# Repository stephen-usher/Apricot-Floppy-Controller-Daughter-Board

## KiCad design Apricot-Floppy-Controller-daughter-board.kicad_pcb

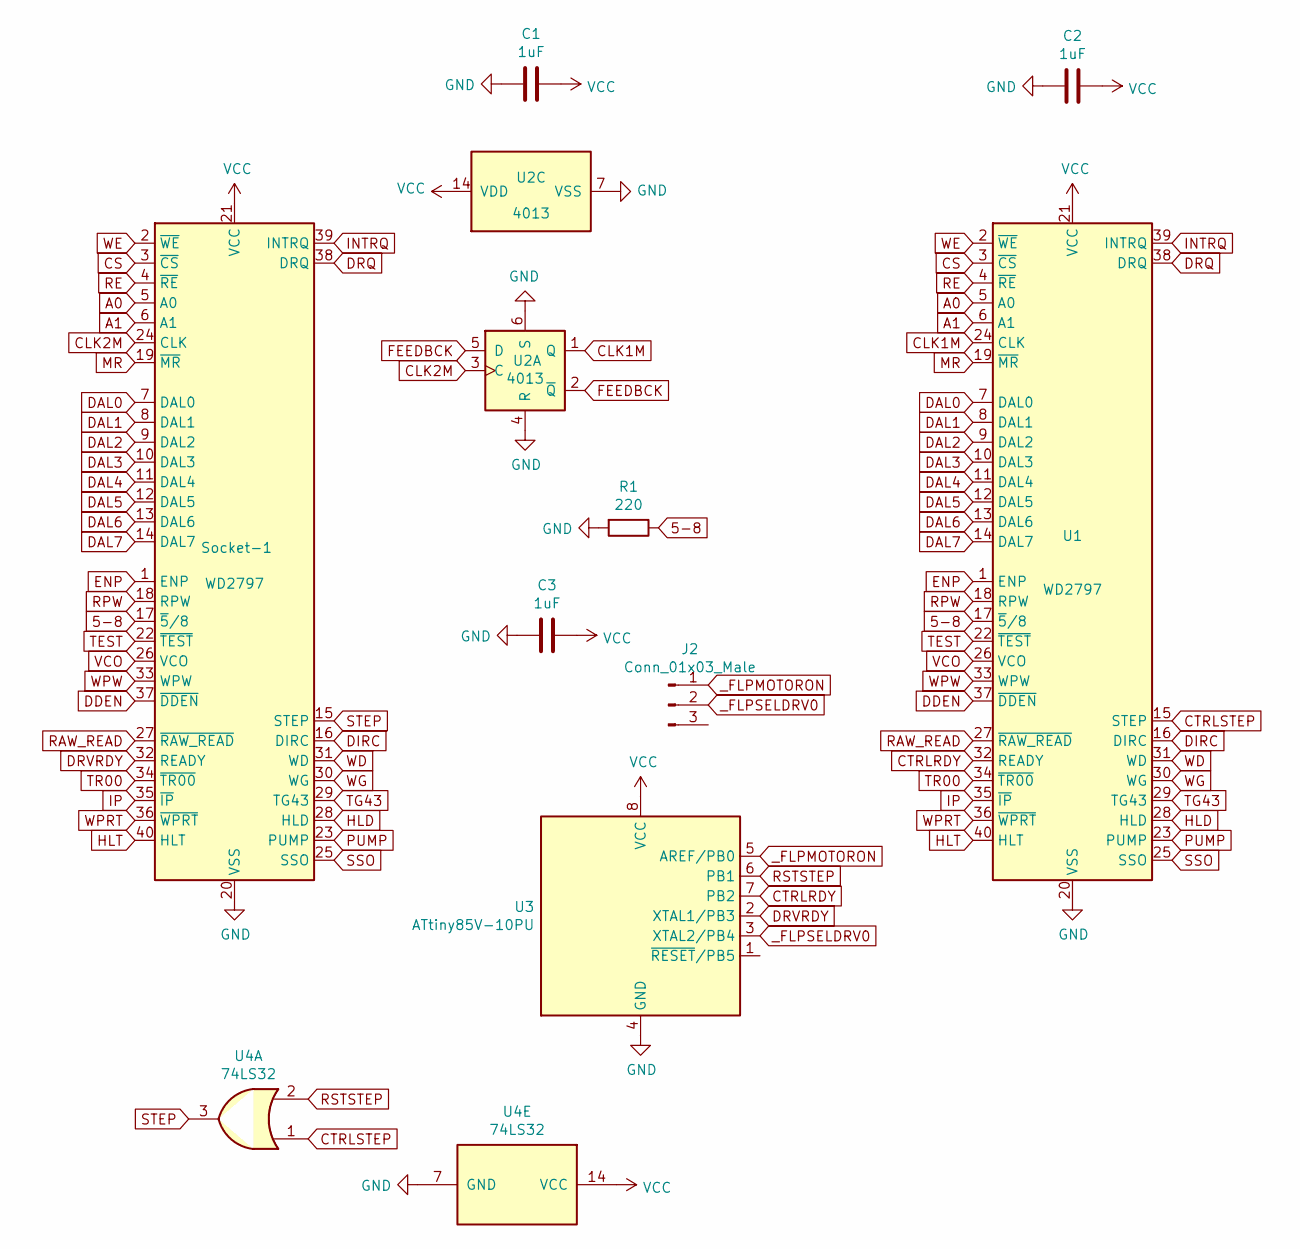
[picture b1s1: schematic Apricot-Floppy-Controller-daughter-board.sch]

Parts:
C1, C2, C3: 1uF; R_0603_1608Metric
J2: Conn_01x03_Male; PinHeader_1x03_P2.54mm_Vertical
R1: 220; R_Axial_DIN0207_L6.3mm_D2.5mm_P7.62mm_Horizontal
Socket-1: WD2797; DIP-40_W15.24mm
U1: WD2797; DIP-40_W15.24mm
U2: 4013; DIP-14_W7.62mm
U3: ATtiny85V-10PU; DIP-8_W7.62mm
U4: 74LS32; DIP-14_W7.62mm

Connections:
5-8: R1.1, Socket-1.17 (~5~/8), U1.17 (~5~/8)
A0: Socket-1.5 (A0), U1.5 (A0)
A1: Socket-1.6 (A1), U1.6 (A1)
CLK1M: U1.24 (CLK), U2.1 (Q)
CLK2M: Socket-1.24 (CLK), U2.3 (C)
CS: Socket-1.3 (~CS), U1.3 (~CS)
CTRLRDY: U1.32 (READY), U3.7 (PB2)
CTRLSTEP: U1.15 (STEP), U4.1
DAL0: Socket-1.7 (DAL0), U1.7 (DAL0)
DAL1: Socket-1.8 (DAL1), U1.8 (DAL1)
DAL2: Socket-1.9 (DAL2), U1.9 (DAL2)
DAL3: Socket-1.10 (DAL3), U1.10 (DAL3)
DAL4: Socket-1.11 (DAL4), U1.11 (DAL4)
DAL5: Socket-1.12 (DAL5), U1.12 (DAL5)
DAL6: Socket-1.13 (DAL6), U1.13 (DAL6)
DAL7: Socket-1.14 (DAL7), U1.14 (DAL7)
DDEN: Socket-1.37 (~DDEN), U1.37 (~DDEN)
DIRC: Socket-1.16 (DIRC), U1.16 (DIRC)
DRQ: Socket-1.38 (DRQ), U1.38 (DRQ)
DRVRDY: Socket-1.32 (READY), U3.2 (XTAL1/PB3)
ENP: Socket-1.1 (ENP), U1.1 (ENP)
FEEDBCK: U2.2 (~Q), U2.5 (D)
GND: C1.2, C2.2, C3.2, R1.2, Socket-1.20 (VSS), U1.20 (VSS), U2.4 (R), U2.6 (S), U2.7 (VSS), U3.4 (GND), U4.7 (GND)
HLD: Socket-1.28 (HLD), U1.28 (HLD)
HLT: Socket-1.40 (HLT), U1.40 (HLT)
INTRQ: Socket-1.39 (INTRQ), U1.39 (INTRQ)
IP: Socket-1.35 (~IP), U1.35 (~IP)
MR: Socket-1.19 (~MR), U1.19 (~MR)
PUMP: Socket-1.23 (PUMP), U1.23 (PUMP)
RAW_READ: Socket-1.27 (~RAW_READ), U1.27 (~RAW_READ)
RE: Socket-1.4 (~RE), U1.4 (~RE)
RPW: Socket-1.18 (RPW), U1.18 (RPW)
RSTSTEP: U3.6 (PB1), U4.2
SSO: Socket-1.25 (SSO), U1.25 (SSO)
STEP: Socket-1.15 (STEP), U4.3
TEST: Socket-1.22 (~TEST), U1.22 (~TEST)
TG43: Socket-1.29 (TG43), U1.29 (TG43)
TR00: Socket-1.34 (~TR00), U1.34 (~TR00)
VCC: C1.1, C2.1, C3.1, Socket-1.21 (VCC), U1.21 (VCC), U2.14 (VDD), U3.8 (VCC), U4.14 (VCC)
VCO: Socket-1.26 (VCO), U1.26 (VCO)
WD: Socket-1.31 (WD), U1.31 (WD)
WE: Socket-1.2 (~WE), U1.2 (~WE)
WG: Socket-1.30 (WG), U1.30 (WG)
WPRT: Socket-1.36 (~WPRT), U1.36 (~WPRT)
WPW: Socket-1.33 (WPW), U1.33 (WPW)
_FLPMOTORON: J2.1, U3.5 (AREF/PB0)
_FLPSELDRV0: J2.2, U3.3 (XTAL2/PB4)

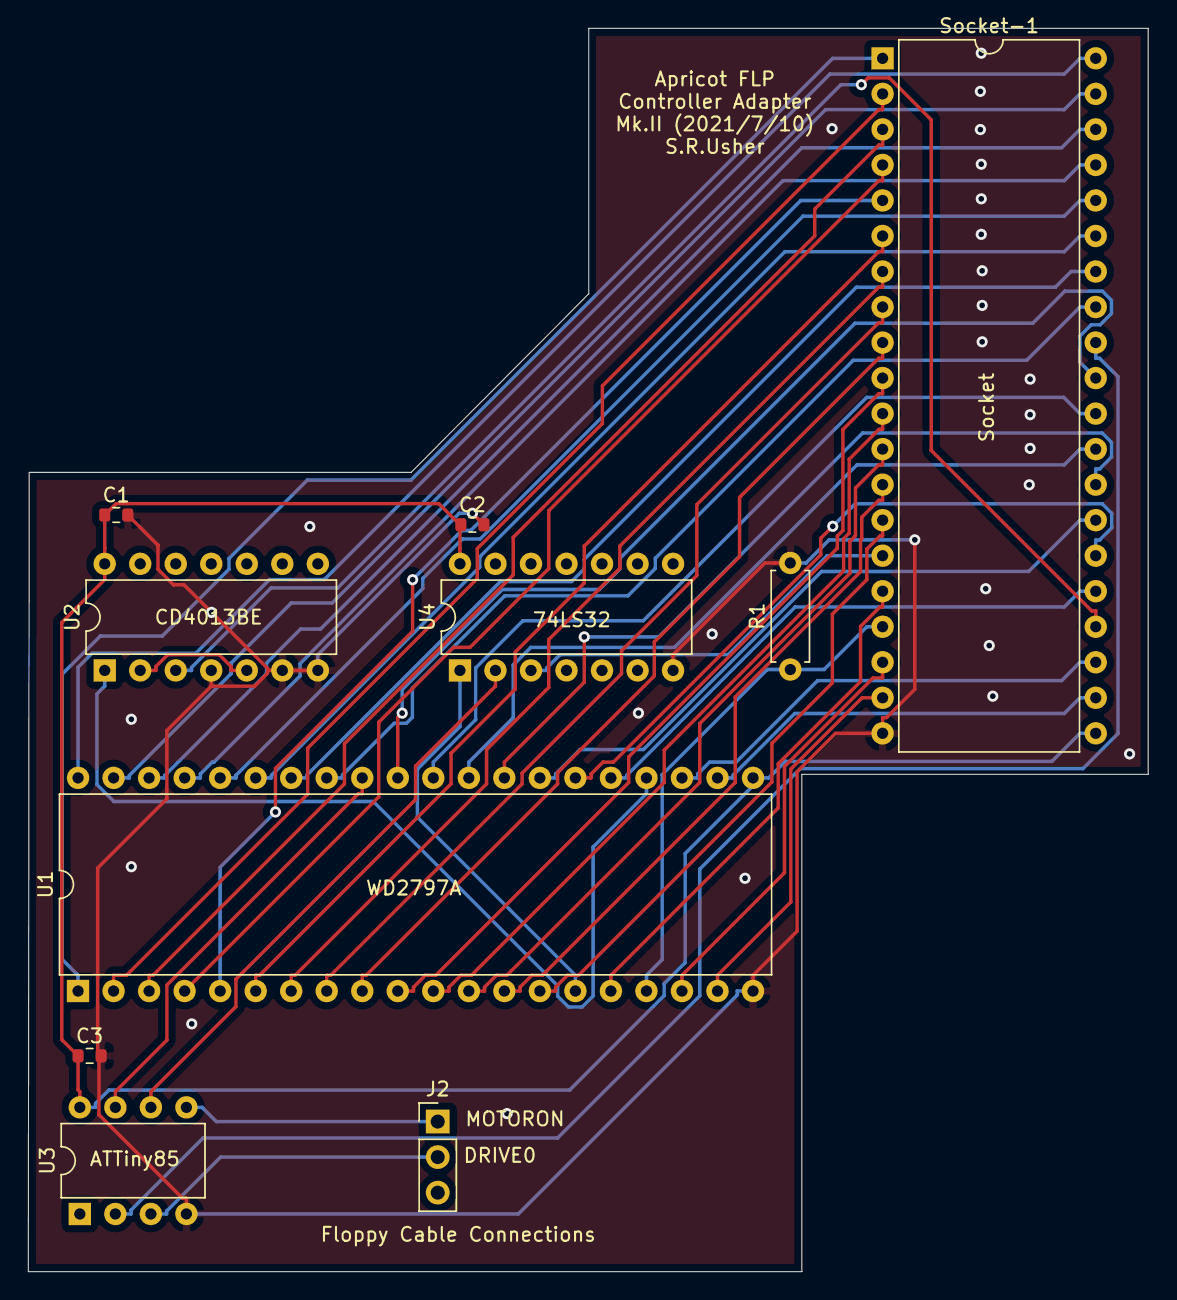
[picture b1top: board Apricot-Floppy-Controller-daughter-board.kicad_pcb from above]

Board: 2 copper layers, 80.1 x 88.9 mm, 10 parts (0 on the bottom side), 47 nets.

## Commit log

2023-03-26 Added Arduino code
